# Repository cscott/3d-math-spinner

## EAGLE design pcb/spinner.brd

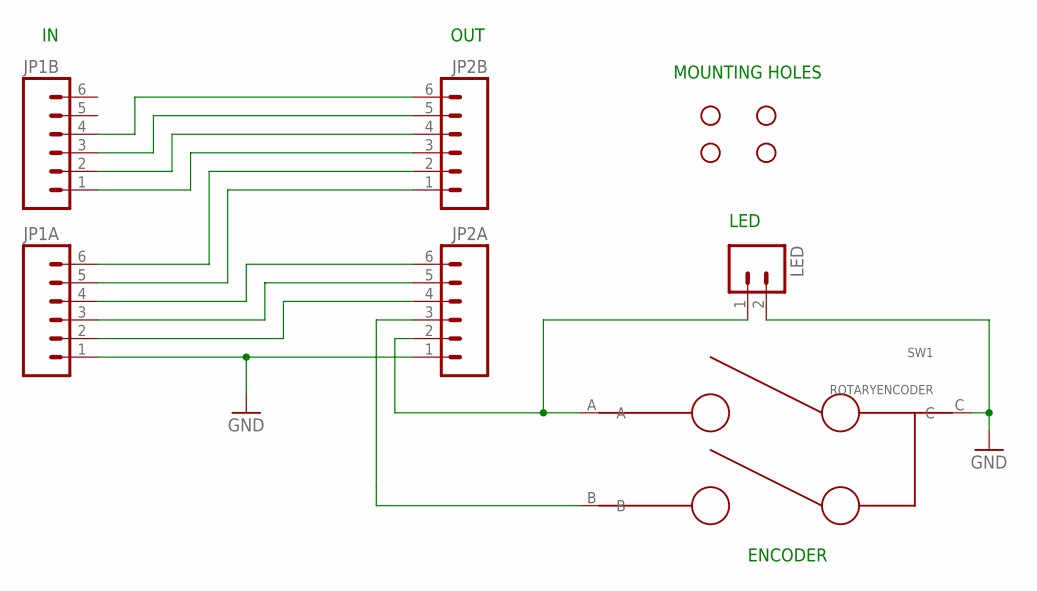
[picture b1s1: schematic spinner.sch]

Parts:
JP1A, JP1B, JP2A, JP2B: M06LONGPADS; 1X06_LONGPADS
JP3, JP4, JP5, JP6: STAND-OFF
LED: M02PTH3; 1X02_LONGPADS
SW1: ROTARYENCODER; EVQV5

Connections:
GND: JP1A.1, JP2A.1, LED.2, SW1.C
unnamed: JP2A.2, LED.1, SW1.A
unnamed: JP1B.4, JP2B.6
unnamed: JP1B.3, JP2B.5
unnamed: JP1B.2, JP2B.4
unnamed: JP1B.1, JP2B.3
unnamed: JP1A.6, JP2B.2
unnamed: JP1A.5, JP2B.1
unnamed: JP1A.4, JP2A.6
unnamed: JP1A.3, JP2A.5
unnamed: JP1A.2, JP2A.4
unnamed: JP2A.3, SW1.B

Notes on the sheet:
ENCODER
LED
OUT
MOUNTING HOLES

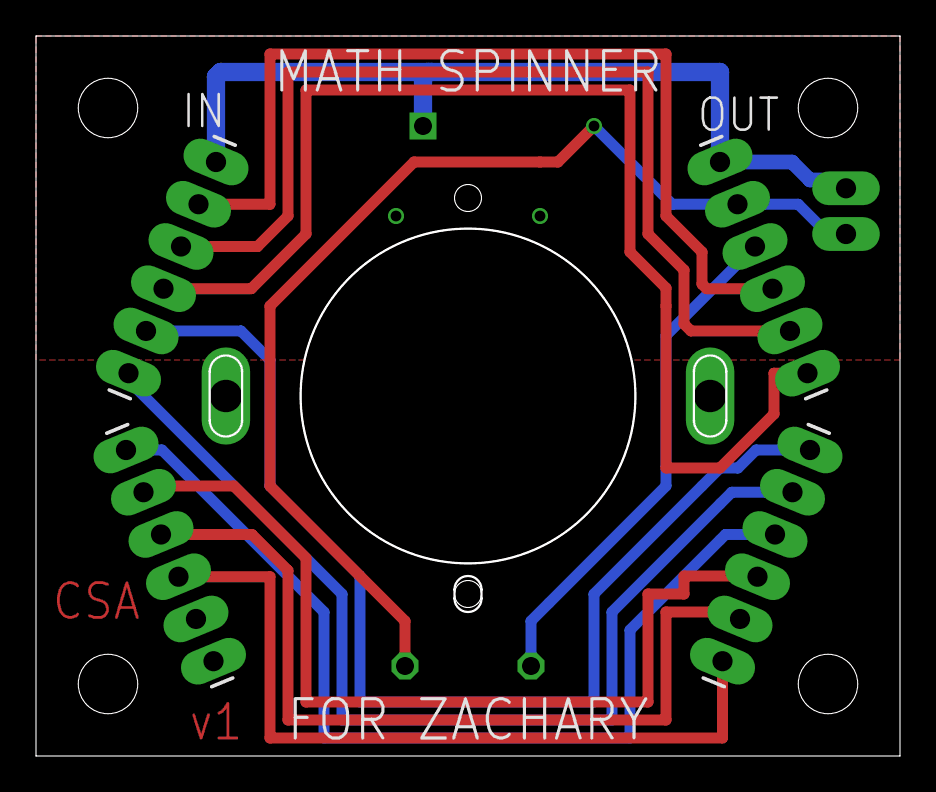
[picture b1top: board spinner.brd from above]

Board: 2 copper layers, 47.9 x 39.9 mm, 10 parts (0 on the bottom side), 12 nets.

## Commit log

2018-05-20 First draft of an electronic math spinner for Zachary.
2018-05-22 change PCB size; add electronics features to end ring & lid.
2018-05-22 Change the thick rings to be the middle and end ones.
2018-06-01 more improvements.
2018-06-01 Add render script.
2018-06-05 Remove unused ring1d
2018-06-05 Enlarge space for LED leads in red ring.
2018-06-05 Add arduino code.
2018-06-05 Check in STLs.
2018-06-05 Check in rotary encoder PCBs.

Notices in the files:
parts and their libraries:
SparkFun: Licensing: CC v3.0 Share-Alike You are welcome to use this library for commercial purposes.
